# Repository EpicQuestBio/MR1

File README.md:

# MR1 Nanopore Reader (MR1)

[-brightgreen.svg)](#testing--verification)

The **MR1 Nanopore Reader** is an open-source, ultra-low-noise solid-state and biological nanopore sequencer flow cell, low-current transimpedance amplifier, and automated fluidic control system. It integrates high-precision parametric CAD models (`build123d`), ultra-low-leakage analog front-end electronics (KiCad), an automated dual-pump fluidic handler, and an ESP32-S3 high-speed continuous streaming firmware stack.

## Architecture & Overview
The system uses a complete **4-electrode topology** (Working Electrode `WE_POS` / `>PORE_AMP`, Working Sense `WS_CIS` & `WS_CIS_WIDE`, Reference Electrode `RE_TRANS`, Counter Electrode `CE_GNDA`) combined with explicitly driven guards (`GUARD`, `GUARD_WIDE`, `GUARD_CIS_A`, `GUARD_CIS_B`) across a distributed 12-pin interface ($36\text{ mm}$ span) to achieve sub-picoampere sensitivity, neutralize stray capacitance, and distribute mechanical spring forces across the PTFE substrate.

The architecture consists of:
- **Headstage Hardware**: A custom, low-parasitic PTFE/Rogers interposer cartridge that seats a 4x4mm nanopore wafer clamped within silicone PDMS gaskets. It interfaces via gold-plated pogo pins to a low-bias-current transimpedance amplifier (LMP7721) mounted beneath the flowcell.
- **Reader Hardware (MR1)**: An ESP32-S3-driven core processing node operating a continuous 100 kHz SPI DMA data acquisition sequence, dual DACs for precision transmembrane voltage bias, and USB CDC-ACM streaming logic.
- **Pump / Power Subsystem**: A dedicated USB-PD powered board managing automated fluidic dispensing (peristaltic motors), pressure sensing, and SBU-based I2C communication back to the main MR1 host.
- **Data Ingestion Pipeline**: High-throughput IPC software utilizing python scripts (`daq_client.py`) and zeroMQ / WebSocket endpoints to reliably process, structure, decode, and log the real-time electrical data for machine learning basecalling or browser visualization.

## Setup & Prerequisites
To build, modify, or interact with this repository, ensure your environment meets these requirements.

### Toolchain Prerequisites
- **Python**: 3.10+
- **KiCad**: Version 7.0+ (For PCB design modifications and scripting exports)
- **PlatformIO Core (CLI)**: For firmware compilation (`pio run`)
- **OpenSCAD / build123d**: For generating solid body parts.
- **Node.js**: v18+ (For UI and test automation dependencies)

### Environment Setup
Run the bootstrap setup scripts depending on your OS to establish a clean python virtual environment and node module cache.
```bash
# On Linux/macOS
./setup_env.sh

# On Windows (PowerShell)
.\setup_env.ps1
```

Activate the python virtual environment:
```bash
source .venv/bin/activate
```

### Build & Test
You can trigger the comprehensive unit, integration, and dimension-parity tests using the included test suite.
```bash
# Ensure you have activated the virtual environment and built assets
python run_tests.py
# Or directly via pytest
pytest tests/
```

To build and upload firmware to the MR1 reader or the Pump board:
```bash
# Navigate to the target directory
cd MR1_firmware  # or cd Pump_firmware
pio run --target upload
```

## License

This project is dedicated to the public domain under the **CC0 1.0 Universal (CC0 1.0) Public Domain Dedication**.

Created by Lawrence R. Kincheloe III / Molecular Reality Corp (2026).
See the `LICENSE` file for the full text.

---

## Table of Contents

- [Architecture & Overview](#architecture--overview)
- [Setup & Prerequisites](#setup--prerequisites)
- [License](#license)
- [System Architecture](#system-architecture)
- [Project Structure](#project-structure)
- [Quick Start & Environment Setup](#quick-start--environment-setup)
- [Deliverables & Export System](#deliverables--export-system)
- [Hardware Build Pipeline & Board Status](#hardware-build-pipeline--board-status)
- [OpenAuto-CFD & Co-Design](#openauto-cfd--co-design)
- [3D Visualizer & Interactive Inspection](#3d-visualizer--interactive-inspection)
- [KiCad Action Plugin & CLI](#kicad-action-plugin--cli)
- [Testing & Verification](#testing--verification)
- [Hardware & Electronics](#hardware--electronics)
- [ESP32-S3 Firmware](#esp32-s3-firmware)
- [Fluidic Routing & Mold Casting](#fluidic-routing--mold-casting)
- [Documentation Index](#documentation-index)

## System Architecture

```
                       +---------------------------------------+
                       |           Host PC / Laptop            |
                       |  (High-Throughput Binary Telemetry)   |
                       +-------------------+-------------------+
                                           | J1_HOST (USB-C Cable: USB-PD Sink + High-Speed Data)
                                           v
                       +---------------------------------------+
                       |      Pump Module Board (Pump/)        |
                       |  - STUSB4500 Autonomous USB-PD Sink   |
                       |  - TS3USB221 USB 2.0 Streaming Pass   |
                       |  - STM32G431 Control MCU @ 170 MHz    |
                       |  - Dual Honeywell ABP2 Pressure Sens  |
                       |  - Dual DRV8837C Peristaltic Drivers  |
                       |  - Clean Regulated 5V Output Filter   |
                       +-------------------+-------------------+
                                           | J2_MR1 (USB-C Link: +5V_MR1_CLEAN + SBU I2C + USB)
                                           v
                       +---------------------------------------+
                       |         ESP32-S3 MCU (MR1)            |
                       |  Core 1: ADC SPI DMA & USB CDC Stream |
                       |  Core 0: Web Server, Leak & Pump Ctrl |
                       +---------+-------------------+---------+
                                 |                   |
            SPI Bus (100 kHz)    |                   | UART (J22) / SBU I2C
                                 v                   v
     +-----------------------------+        +--------------------------+
     |     AD40xx 16/18-Bit ADC    |        |  Dual Peristaltic Pumps  |
     |   LMP7721 Ultra-Low-Noise   |        |  (Cis & Trans Chambers)  |
     |     Cartridge Amplifier     |        +--------------------------+
     +--------------+--------------+
                    | Gold Pogo Pins (Ultra-low noise shielded)
                    v
     +---------------------------------------------------------+
     |              Hexagonal Cartridge Flow Cell              |
     |  - Cis & Trans Fluidic Chambers ('X' microfluidic)      |
     |  - Cast Silicone Gasket with Nanopore Silicon Wafer     |
     |  - M75x8mm Clamping Torque Cap & Pressure Puck          |
     |  - Conductive Weep Moat / Leak Detection Sensor         |
     +---------------------------------------------------------+
```

---

## Project Structure

```
mr1/
├── src/                          # Parametric CAD models (build123d / Python)
│   ├── cartridge.py              # Flow cell cartridge stack & PCB models
│   ├── housing.py                # Reader and Pump housings, lids, mounting
│   ├── nanopore_wafer_mold.py    # Interlocking two-part resin casting mold
│   ├── torque_cap.py             # M75/M76 ratcheting torque limiter cap
│   ├── adapters.py               # Luer-lock and threaded NPT fluidic adapters
│   ├── connectors.py             # USB-C, JST XH, and bulkhead panel mounts
│   ├── assembly.py               # Full 3D assembly & 3D spline routing sweeps
│   ├── collision_check.py        # Automated 3D BREP collision & clearance checker
│   └── constants.py              # Central engineering & physical parameters
├── MR1/                          # KiCad 10.0 project for Main Reader Board (4-Layer)
├── Amplifier/                    # KiCad 10.0 project for Cartridge Transimpedance Amp (2-Layer)
├── Pump/                         # KiCad 10.0 project for Pump Controller & USB-PD Hub (4-Layer)
├── MR1_firmware/                 # ESP32-S3 C++ firmware (PlatformIO)
│   ├── include/                  # Pinout mapping, binary protocol framing, web portal
│   ├── src/hal/                  # AD40xx SPI DMA ADC, MCP4822 DAC, Leak Detector
│   ├── src/comm/                 # High-speed USB CDC streaming & UART Pump protocol
│   └── src/web/                  # Embedded Web Portal with WebSocket Oscilloscope
├── wiring/                       # WireViz electrical and fluidic harness specs
│   ├── reader_wiring.yaml        # USB-C, motor, and analog pogo wiring harnesses
│   └── reader_tubing.yaml        # FEP, PharMed BPT, and silicone fluidic tubing specs
├── tests/                        # Automated unit, CAD bounds, firmware, and E2E tests
│   ├── test_geometry.py          # Geometric validity and collision regression
│   ├── test_golden_stl_bounds.py # Dimensional assertions against golden models
│   ├── test_connector_bounds.py  # Connector mounting dimensional checks
│   ├── test_firmware_protocol.py # Binary framing, CRC-16, and DAC mapping tests
│   └── test_exports_e2e.py       # Full deliverables validation (141 files)
├── scripts/                      # Build, export, and testing automation
│   ├── export_manager.py         # Universal multi-domain export orchestrator
│   ├── export_all.sh             # POSIX bash export runner
│   └── run_e2e_tests.sh          # POSIX bash end-to-end test runner
├── exports/                      # Generated release deliverables & manifest
├── requirements.txt              # Pinned Python virtual environment dependencies
├── setup_env.sh                  # Virtual environment manager (Linux/macOS/Bash)
├── setup_env.ps1                 # Virtual environment manager (Windows PowerShell)
├── Makefile                      # Standard project build and export targets
├── EXPORTS.md                    # Detailed deliverables and ordering documentation
├── BOM.md                        # Mechanical bill of materials & sourcing links
└── CASTING.md                    # PDMS/Silicone flow cell casting guidelines
```

---

## Quick Start & Environment Setup

### 1. Initialize Python Virtual Environment

The project uses a local virtual environment (`.venv`) for all Python CAD generation, export pipelines, and test suites.

**On Windows (PowerShell):**
```powershell
.\setup_env.ps1
```

**On Linux / macOS / Git Bash:**
```bash
chmod +x setup_env.sh install.sh
./setup_env.sh
```

To verify environment health at any time:
```bash
./setup_env.sh --check        # or powershell -File .\setup_env.ps1 -Check
```

### 2. Required External Tools (Optional for specific export domains)
- **KiCad 10.0 CLI** (`kicad-cli`): Required to generate Gerbers, Drill files, Pick & Place CSVs, BOMs, and PDF schematics.
- **Graphviz** (`dot`): Required by WireViz for rendering graphical wiring and tubing diagrams.
- **PlatformIO Core** (`pio`): Required to compile ESP32-S3 firmware binaries.

---

## Deliverables & Export System

The repository features an automated multi-domain export orchestrator (`scripts/export_manager.py`) managed via GNU Make, shell scripts, or npm:

### Common Commands

```bash
# Export all project deliverables (CAD, KiCad, Wiring, Firmware, and Manifest)
make export

# Or export specific domains
make export-cad        # 3D Solids (STEP/STL) & 2D CNC Profiles (DXF)
make export-kicad      # Gerbers, Drill, POS, BOM, and PDF schematics
make export-wiring     # WireViz wiring harness and fluidic diagrams
make export-firmware   # Compile and stage ESP32-S3 firmware binaries

# Verify manifest and deliverables
make check             # Verify all 141 indexed deliverables exist on disk
make test              # Run unit tests and CAD collision clearance checks
make test-e2e          # Run end-to-end deliverables validation test
```

### Generated Deliverables Inventory (`exports/`)
- **30 STL Meshes**: Ready for 3D printing (SLA resin molds, TPU pusher plates, PETG housings, and PTFE interposer models).
- **22 STEP Models**: Parametric BREP solids for mechanical assembly and CAD exchange.
- **13 DXF Profiles**: 2D profiles for CNC milling polypropylene sheet stock and synchronizing KiCad PCB `Edge.Cuts` (including `Interposer_DXF.dxf` and `Plate_2_Channel_DXF.dxf`).
- **Fab-Ready PCB Archives**: `MR1_Gerbers.zip` (4-layer main board) and `Amplifier_Gerbers.zip` (2-layer amplifier).
- **Manufacturing Documentation**: Pick-and-Place (POS) coordinates, BOM CSVs, and multi-sheet schematic PDFs.
- **Harness Documentation**: WireViz diagrams for internal wiring and 1/8" barb fluidic tubing.
- **ESP32-S3 Firmware**: Staged `firmware.bin`, `bootloader.bin`, and `partitions.bin`.
- **SHA-256 Manifest**: `exports/manifest.json` tracks file sizes and cryptographic hashes for all 159 files for drift detection.

See [EXPORTS.md](EXPORTS.md) for full details and PCB fabrication recommendations.

---

## Hardware Build Pipeline & Board Status

Automated code scanners and reviewers sometimes mistake the repository's PCB source files for static production-ready layouts. The MR1 hardware design pipeline relies on two fundamental principles:

1. **Dynamic Artifact Generation**:
   The `.kicad_pcb` layout files and downstream fabrication deliverables (Gerber layers, NC drill files, BOMs, Pick and Place POS files, multi-sheet PDF schematics) are dynamically generated and reconciled via the repository's automation pipeline (`scripts/export_manager.py`, Python footprint/layout generators, and `kicad-cli`), rather than being maintained as static hand-edited binaries in the working tree.

2. **Current Board Layout & Routing Status**:
   - **`MR1` Main Reader Board** (`MR1/`): 111 footprints placed, placement complete, 0 routed copper tracks.
   - **`Amplifier` Cartridge Board** (`Amplifier/`): 48 footprints placed, placement complete, 0 routed copper tracks.
   - **`Interposer` Microfluidic Board** (`Interposer/`): 33 footprints placed, 9 routed segments.
   - **`Pump` Controller Board** (`Pump/`): 18 footprints placed, procedurally generated stubs — STM32 QFN-48 currently a 1-pad stub with passives and 3D models pending per [`TODO.md`](TODO.md) §22.

For details on Gerber archiving, dynamic export workflows, and hardware version tags, see the [Artifact & Gerber Release Policy in EXPORTS.md](EXPORTS.md#artifact--gerber-release-policy).

---

## OpenAuto-CFD & Co-Design

The **MR1 Nanopore Reader** incorporates the **OpenAuto-CFD** co-design framework ([`openauto.project.json`](openauto.project.json) / [`atlas.project.json`](atlas.project.json)) to bridge Electrical CAD (KiCad), Mechanical CAD (Build123d / OpenSCAD), and Microfluidic Multiphysics into a single automated pipeline.

### Why OpenAuto-CFD?
Nanopore sensing demands precise hydrodynamic and electro-chemical alignment:
1. **Laminar Stokes Flow ($\text{Re} \ll 1$):** With $50\,\mu\text{m} \times 25\,\mu\text{m}$ channels and $10\,\mu\text{L/min}$ delivery, OpenAuto-CFD calculates viscous pressure drops ($\Delta P \approx 6.2\text{ kPa}$) and eliminates turbulent vortex formation.
2. **SiN Membrane Burst Safety:** Free-standing $20\text{ nm}$ silicon nitride membranes rupture at differential pressures $\Delta P_{\text{burst}} \sim 10\text{ mbar}$. OpenAuto-CFD co-simulation balances hydrodynamic resistance across Cis and Trans chambers to prevent wafer fracture.
3. **Dead-Volume & Bubble Prevention:** Eliminates stagnation recirculation zones ($\vec{v} < 0.01 \cdot v_{\text{bulk}}$) that trap air microbubbles or cause analyte sample carryover.
4. **Concentric Kelvin Cell Coupling:** Aligns the 4-electrode Kelvin sensing array on the PTFE interposer directly with the microfluidic chamber aperture.

See the comprehensive [OpenAuto-CFD Guide](docs/OPENAUTO_CFD.md) for full physical derivations and co-simulation specs.

---

## 3D Visualizer & Interactive Inspection

The repository provides a rich multi-layer 3D visualizer powered by `build123d` and `ocp_viewer`:

```bash
# Launch interactive 3D assembly visualizer
npm run visualize
# Or via Python directly:
python src/assembly.py

# Or launch via install script diagnostic flag:
./install.sh --viewer
```

### Visualizer Features
- **Full System Assembly:** Displays the Peristaltic Pump base module, Reader Housing & Tower, 4× Luer Bulkhead Panel Mounts, 7-layer Cartridge Stack (Bottom Pusher Plate, Base Hex Plate, Fitted Gasket, Active PCB, Wafer Gasket, Top Hex Plate, Pressure Puck), and Torque-Lock Cap.
- **3D Swept Tubing Routes:** Renders actual 3D splines for all 5 fluidic paths (`TUBE_PUMP`, `TUBE_FEED`, `TUBE_TRANS_LINE`, `TUBE_WASTE_1`, `TUBE_WASTE_2`) with verified bend radii.
- **X-Ray & Clipping Plane Inspection:** Enables cross-sectional slicing to verify internal gasket compression and pogo pin deflection.
- **WireViz Electrical & Tubing Harnesses:** Generates SVG and HTML diagrams for internal wiring (`wiring/reader_wiring.yaml`) and fluid lines (`wiring/reader_tubing.yaml`) via `npm run export:wiring`.
- **Automated 360° Flythrough Video:** Renders photorealistic rotating orbits using PyVista VTK via `npm run render:flythrough`.

---

## KiCad Action Plugin & CLI

The repository includes a dedicated KiCad Action Plugin and CLI verification engine ([`plugins/openauto_cfd_plugin.py`](plugins/openauto_cfd_plugin.py)) ensuring PCB layouts strictly comply with mechanical, fluidic, and manifest constraints.

### How to Install the Plugin into KiCad
```bash
# Install plugin into active KiCad installation (~/.local/share/kicad/ or %APPDATA%/kicad/)
npm run openauto:install-plugin
# Or via Python:
python plugins/openauto_cfd_plugin.py --install
```

### Using Inside KiCad PCB Editor (GUI)
1. Open any board (`Amplifier.kicad_pcb`, `MR1.kicad_pcb`, `Pump.kicad_pcb`, or `Interposer.kicad_pcb`).
2. Navigate to **Tools $\to$ External Plugins $\to$ OpenAuto-CFD: Co-Design & Clearance Verifier**.
3. The plugin parses the board, checks Edge.Cuts continuity, verifies bounding dimensions against `openauto.project.json`, and displays a comprehensive verification report.

### Standalone CLI & CI/CD Verification
```bash
# Validate all 4 boards in headless mode (Edge.Cuts continuity, dimensions, and net mapping)
npm run openauto:validate

# Synchronize Edge.Cuts dimensions back into the openauto.project.json manifest
npm run openauto:sync
```

---

## Testing & Verification

The project enforces zero physical interference and strict dimensional fidelity across all hardware interfaces:

```bash
# Run the complete test suite (Unit Tests, Collision Checks, Firmware Protocol, Parity, and E2E)
python run_tests.py
```

### Automated Validation Includes:
1. **Golden STL & PCB Bounds**: Asserts dimensions of all generated CAD models against benchmark constraints.
2. **BREP Collision Clearance (6 Independent Suites)**:
   - Cartridge stack component alignment.
   - Housing and lid clearances.
   - M75×8mm external / M76×8mm internal helical thread engagement (0 interference volume).
   - PCB standoff clearances against fluidic lines.
   - Internal component clearance (wiring vs. cartridge solids).
   - Flexible routing collision sweeps against module envelopes.
3. **Spline Bend Radius Validation**: Computes instantaneous curvature along swept routes and verifies compliance with minimum bend radii (Silicone/FEP tubing $\ge 10\text{ mm}$, Wiring $\ge 10\text{ mm}$).
4. **CAD Feature Validation Suite**: Validates 80x60mm rectangular motherboard, hexagonal carrier frame, circular nanopore carrier, mold modes, lid cutouts, and pump case bosses.
5. **Firmware Protocol Tests**: CRC-16 integrity, binary packet serialization (`StreamFrame`), pump packet XOR checksums, and DAC voltage-to-code mapping.
6. **E2E Deliverables Tests**: Validates headers, non-zero file sizes, and SHA-256 hashes of all 159 export deliverables.

---

## Hardware & Electronics

- **MR1 Main Controller Board** (`MR1/`):
  - 4-Layer stackup:
    - Layer 1 (Top Signal): Component placement, USB D+/D-, SPI traces to FPC, DAC outputs
    - Layer 2 (Ground Plane): Split into GNDA (Quiet Analog Ground) and GND (Digital Ground)
    - Layer 3 (Power Plane): Split into Analog Power (VDDA, VSSA) and Digital Power (+3V3, VBUS)
    - Layer 4 (Bottom Signal): Secondary routing, low-speed housekeeping, and auxiliary pours
  - ESP32-S3-MINI-1U MCU with native high-speed USB CDC.
  - Dedicated SPI bus for high-speed ADC sampling.
  - Dual MCP4822 12-bit DACs providing bipolar pore bias voltages (-1.587V to +1.587V) and unblocking pulses.
  - Conductive weep-hole leak detection sensing on GPIO1.
- **PTFE Interposer Circuit Board** (`Interposer/` & `src/cartridge.py`):
  - 55.0 × 51.962 × 0.8 mm hexagonal substrate fabricated on ultra-low-loss PTFE / Rogers RO4350B.
  - Physical and electrical barrier dividing Cis (top) and Trans (bottom) microfluidic chambers.
  - Dual-sided silver chloride (Ag/AgCl) ribbon electrode pads positioned inside the Cis ($30^\circ$) and Trans ($210^\circ$) flow channels.
  - Central 6.20 × 6.20 mm diamond cutout ($45^\circ$) allowing the silicone gasket protrusion to seal directly around the silicon nanopore wafer.
  - 12-pin guarded ENIG landing array (`PogoPin_Target_12Pin_Distributed`) flanking high-impedance sense lines (`WS_CIS`, `RE_TRANS`) with driven low-impedance `GUARD` pins.
  - Hermetically clamped between `Cast_Nanopore_Wafer_Gasket` (top) and `Fitted_Amplifier_Gasket` (bottom).
- **Cartridge Transimpedance Amplifier** (`Amplifier/`):
  - 2-Layer 0.8 mm ultra-thin board designed for direct insertion into the flow cell stack.
  - LMP7721 ultra-low input bias current amplifier (sub-femtoampere leakage).
  - Low-leakage guard rings and driven shields guarding the high-impedance nanopore input node.
  - Direct connection to flow cell via gold-plated Mill-Max pogo pins.
- **Pump Controller & USB-PD Hub Board** (`Pump/` & `src/cartridge.py`):
  - 4-Layer 1.6 mm board (88.0 × 88.0 mm) fitting within the `Housing_Pump_Case` internal pocket.
  - **Dual USB-C Receptacles**:
    - `J1_HOST` at $X = -15.0\text{ mm}$ (top edge): USB-PD Sink + Host laptop data interface.
    - `J2_MR1` at $X = +15.0\text{ mm}$ (top edge): Regulated clean 5V power output to MR1 Reader + SBU I2C control link.
    - Perfectly aligned to the $12 \times 6\text{ mm}$ cutouts on `Housing_Pump_Case` rear wall ($Y = 55.0\text{ mm}$).
  - **High-Speed USB 2.0 Pass-Through**: TI TS3USB221 multiplexer (>1.1 GHz bandwidth, insertion loss < 0.5 dB) passes 100 kHz continuous ADC telemetry straight through to the laptop without MCU latency.
  - **STUSB4500 Autonomous USB-PD Sink**: Automatically negotiates 9V/12V/15V/20V profiles from USB-PD power sources.
  - **Clean +5V Output Subsystem**: Synchronous step-down buck converter (36V/3A) + TPS22916 soft-start load switch + LC $\pi$-filter ensuring ultra-low ripple 5V power for MR1's analog frontend.
  - **STM32G431CBU6 Control MCU**: ARM Cortex-M4 @ 170 MHz orchestrating precision TIM1 PWM peristaltic velocity control, I2C telemetry, and hardware emergency stop gating.
  - **Dual Honeywell TruStability / ABP2 Pressure Transducers**:
    - Transducer 1 (0-15 psi gauge): Real-time pressure monitoring on Cis chamber feed line.
    - Transducer 2 (0-5 psi gauge): Real-time pressure monitoring on Trans chamber recirculation line.
  - **Dual TI DRV8837C Motor Drivers**: 1.8A peak H-bridge drivers with hardware shutdown interlock directly connected to the weep moat leak detector.

---

## ESP32-S3 Firmware

Located in `MR1_firmware/` (ESP32-S3 Main Reader) and `Pump_firmware/` (STM32G431 Peristaltic Pump & USB-PD Hub):
- **Dual-Core Architecture**:
  - **Core 1**: Dedicated to continuous 100 kHz SPI DMA ADC sampling and high-throughput USB CDC streaming.
  - **Core 0**: Handles Wi-Fi AP/station management, AsyncWebServer, WebSocket oscilloscope telemetry, and pump control.
- **High-Throughput Binary Protocol**: Frames of 64 decimated/raw samples packed with sequence IDs, 64-bit microsecond timestamps, and CRC-16 checksums.
- **USB-C SBU Auto-Polarity Detection**: Dynamic GPIO-matrix sensing on SBU1/SBU2 pins automatically determines clock (SCL) and data (SDA) orientation for I2C communication to external pump modules, working seamlessly regardless of cable flip.
- **Embedded Web Oscilloscope**: Live HTML5 Canvas visualization accessible via browser over Wi-Fi without needing host drivers.

### Host 100 kHz Streaming DAQ Client (`scripts/daq_client.py`)

A high-performance Python client for acquiring continuous 100 kHz binary telemetry from the MR1 Reader:

```bash
# Live acquisition with terminal dashboard and CSV logging
python scripts/daq_client.py --port COM3 --bias 180.0 --output data.csv

# Run mock simulation mode (generates baseline ionic current & DNA translocation events)
python scripts/daq_client.py --mock --duration 5.0 --output simulation.csv

# Execute SBU I2C polarity auto-detection and start pump
python scripts/daq_client.py --port COM3 --sbu-detect --pump 60
```

- **Binary Frame Synchronization**: Synchronizes on `"SENT"` magic word (`0x53454E54` / little-endian `b"TNES"`).
- **CRC-16-CCITT Verification**: 100% integrity validation on every 146-byte packet.
- **Pore Current Conversion**: Converts differential 16-bit counts to Amperes ($I_{\text{pore}} = V_{\text{adc}} / R_f$, default $R_f = 1\text{ G}\Omega \implies 1\text{ V}/1\text{ nA}$).
- **Real-Time Telemetry Dashboard**: Live sample rate (kS/s), data throughput (KB/s), dropped frame count, RMS current noise, pump status, and leak monitoring.

---

## Fluidic Routing & Mold Casting

- **Standardized Tubing**: All microfluidic connections standardize on **1/8" ID $\times$ 1/4" OD** tubing and 1/8" hose barb panel-mount fittings.
- **Fluid Lines**:
  - `TUBE_PUMP`: PharMed BPT (0.12 m) — Buffer reservoir $\to$ Peristaltic pump.
  - `TUBE_FEED`: FEP (0.22 m) — Pump $\to$ Cis chamber inlet ($210^\circ$).
  - `TUBE_TRANS_LINE`: PEEK (0.18 m) — Trans chamber outlet ($150^\circ$) $\to$ Waste.
  - `TUBE_WASTE_LINES` ($\times 2$): Silicone (0.25 m) — Cis outlet ($30^\circ$) and Trans inlet ($330^\circ$).
- **Gasket Fabrication**: Two-part resin casting mold (`Nanopore_Wafer_Mold_Left` and `Right`) designed for casting degassed PDMS (Sylgard 184) or high-compliance silicone around the silicon nanopore wafer. See [CASTING.md](CASTING.md) for detailed surface preparation, degassing, and curing procedures.

---

## Documentation Index

### Open Source Governance & Policies
- [CONTRIBUTING.md](CONTRIBUTING.md): Engineering guidelines, code style, and pull request workflow.
- [CODE_OF_CONDUCT.md](CODE_OF_CONDUCT.md): Contributor Covenant v2.1 standards and pledge.
- [SECURITY.md](SECURITY.md): Security vulnerability reporting policy and electrical safety bounds.
- [CITATION.cff](CITATION.cff): Academic citation metadata for research and publications.
- [LICENSE](LICENSE): CC0 1.0 Universal (CC0-1.0) Public Domain Dedication.

### Hardware & Manufacturing Specifications
- [BOM.md](BOM.md): Complete mechanical, fluidic, PCB, and active electronic bill of materials with sourcing links.
- [EXPORTS.md](EXPORTS.md): Complete export deliverables catalog, fab ordering specifications, and drift tracking.
- [CASTING.md](CASTING.md): Engineering guide for casting ultra-low-noise PDMS gaskets.
- [PROJECT.md](PROJECT.md): Project architecture, interface contracts, and milestone tracking.
- [TODO.md](TODO.md): Development roadmap and completed porting phases.

### Firmware & Protocols
- [MR1 Reader Firmware](MR1_firmware/README.md): ESP32-S3 dual-core firmware architecture, SPI DMA ADC, and web oscilloscope.
- [Pump Hub Firmware](Pump_firmware/README.md): STM32G431 peristaltic motor control, STUSB4500 USB-PD, and pressure monitoring.
- [DAQ Streaming Protocol](docs/DAQ_STREAMING_SPEC.md): Binary stream framing, CRC-16 checksums, and 100 kHz sample encoding.
- [MR1 Data Exchange Spec](docs/MR1_DATA_EXCHANGE_SPEC.md): Inter-board SBU I2C and UART communications.
- [Interposer 4-Electrode Spec](docs/INTERPOSER_FOUR_ELECTRODE_SPEC.md): Gamry 4-electrode topology and driven guard architectures.
- [Weep Moat Interlock Spec](docs/ECO_WEEP_SENSE_BUFFER_INTERLOCK.md): Leak detection sensor and hardware power cutoff circuitry.

### Co-Design, Simulation & Tools
- [Micropore & Salt Aperture Configurations](docs/MICROPORE_NACL_CONFIGURATIONS.md): Working configuration matrix and simulation analysis for 10 µm and 100 µm pores in NaCl.
- [Dual-Route TIA Netlist & BOM](docs/DUAL_ROUTE_AMPLIFIER_NETLIST_BOM.md): Complete point-to-point netlist, component tolerances, and recommended manufacturer BOM for Route 1 (LMP7721) and Route 2 (OPA192).
- [OpenAuto-CFD & 3D Visualizer Guide](docs/OPENAUTO_CFD.md): Multiphysics co-simulation, interactive 3D assembly visualizer (`ocp_viewer`), and KiCad action plugin documentation.
- [OpenAuto Project Manifest](openauto.project.json): Single-source-of-truth hardware manifest linking ECAD, MCAD, fluidics, and harnesses.

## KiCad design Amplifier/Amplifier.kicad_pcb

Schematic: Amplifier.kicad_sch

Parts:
C1: 2pF; C_0402_1005Metric; LCSC C161316
C3: 15pF; C_0402_1005Metric; LCSC C33148
C6, C9, C14, C20: 100nF; C_0402_1005Metric; LCSC C49678
C7, C8: 10nF; C_0402_1005Metric; LCSC C1525
C10, C12, C19, C31, C32, C33, C34, C39: 100nF; C_0402_1005Metric; LCSC C15255
C11: 4.7u; C_0402_1005Metric; Manufacturer_Part_Number JMK107C6475KA-T; LCSC C19702
C29, C30: 10pF; C_0402_1005Metric; LCSC C1548
C35: 10u; C_0402_1005Metric; MPN GRM21BR61H106KE43K; LCSC C1713
C40, C42: 100nF; C_0402_1005Metric; Mouser PN 710-885012205037; LCSC C15255
C41: 1nF; C_0402_1005Metric; LCSC C1523
D82: MBR0540; D_SOD-123; MPN MBR0540L-TP; LCSC C5204747
FB1, FB2: HZ0402A152R-10; L_0402_1005Metric; LCSC C442654
J7: Conn_01x14_MountingPin; Amphenol_F32R-1A7x1-11014_1x14-1MP_P0.5mm_Horizontal; LCSC C2856818
NT3, NT4, NT5, NT6, NT7, NT8: NetTie_2; NetTie-2_SMD_Pad0.5mm
P1, P3, P4, P6, P7, P8, P9, P10, P11, P12: PogoPin_MillMax_SMT_1Pin
P2, P5: PogoPin_MillMax_SMT_1Pin_Guarded; PogoPin_SMT_Circle_Guard_Notched
Q3: 2N7002; SOT-23; LCSC C8545
R1: 1G; R_0402_1005Metric; LCSC HVC0805T1007JET
R3, R5: 1K; R_0402_1005Metric; LCSC C17513
R4: 100; R_0402_1005Metric; LCSC C25097
R6, R9: 1K; R_0402_1005Metric; LCSC C25149
R8: 100; R_0402_1005Metric; LCSC C17408
R10, R14, R15: 100k; R_0402_1005Metric; LCSC C60491
R16: 1M; R_0402_1005Metric; LCSC C25488
R27, R41: 27; R_0402_1005Metric; MPN RC0402JR-0727RL; LCSC C25078
R28, R29, R30, R31, R32, R33: 49.9; R_0402_1005Metric; MPN RC0402JR-0727RL; LCSC C4074199
R43, R44, R45, R46: 499 (0.1%); R_0402_1005Metric; LCSC C25132
SYM1: SYM_Arrow45_Large; Fluid_Overlay_SILKSCREEN_ONLY
U2: LMP7721; SOIC-8_3.9x4.9mm_P1.27mm; Mouser PN 926-LMP7721MA/NOPB
U5: OPA2192IDR; SOIC-8_3.9x4.9mm_P1.27mm; MPN OPA2192IDR; LCSC C110074
U6: ADA4940-1xCP; LFCSP-16-1EP_3x3mm_P0.5mm_EP1.3x1.3mm_ThermalVias; MPN ADA4940-1ACPZ-RL; LCSC C529241
U13: AD40xxBRMZ; MSOP-10_3x3mm_P0.5mm; MPN AD4011BCPZ-RL7; LCSC C539308
U14: LP5907MFX-1.8; SOT-23-5; MPN LP5907MFX-1.8/NOPB; LCSC C92498
U16: LTC6268xS8; SO-8_3.9x4.9mm_P1.27mm; MPN LTC6268IS8#TRPBF; LCSC C689169
U17: ADG1219BRMZ; MSOP-8_3x3mm_P0.65mm; MPN ADG1219BRMZ; LCSC C206796

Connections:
+1V8: C11.1, U13.2 (VDD), U14.5 (OUT)
+3.3VA: C33.1, FB1.2, FB2.1, R14.1, U13.10 (VIO)
+3V3: FB1.1, J7.1, U17.1 (EN)
/>PORE_AMP: J7.14, P9.1 (PIN_1)
/CE_GNDA: NT8.1, P7.1 (PIN_1)
/GDAC_CLK: R31.1, U13.8 (SCK)
/GDAC_EN: R29.1, U13.6 (CNV)
/GDAC_SDI: R30.1, U13.9 (SDI)
/GDAC_SDO: R28.1, U13.7 (SDO)
/GNDA_SHLD: P1.1 (PIN_1)
/GUARD: NT3.1, NT5.2, P4.1 (PIN_1), P5.2 (GUARD), P6.1 (PIN_1), U2.2 (NC), U2.7 (NC)
/GUARD_WIDE: NT5.1, P2.2 (GUARD), P3.1 (PIN_1), U5.6 (-), U5.7
/RE_TRANS: P8.1 (PIN_1), R6.2, R9.2
/ROUTE_SEL: R33.1, U17.8 (IN)
/R_WEEP_GATE: D82.1 (K), R15.2, R16.1
/R_WEEP_LIM: P11.1 (PIN_1), R15.1
/R_WEEP_PULL: Q3.3 (D), R14.2, U14.3 (EN)
/Route1_OUT: C9.1, R3.1, U16.6, U17.7 (SA)
/Route2_OUT: R32.2, U17.5 (SB)
/SHIELD: NT7.2
/SHIELD_AMP: J7.MP (MountPin), NT4.2
/Signal_Return: R45.1, U17.6 (D)
/Vbias: C6.1, C14.1, C35.1, NT3.2, R4.1, R6.1, R9.1, U2.1 (+), U5.3 (+), U5.5 (+), U13.1 (REF), U16.1 (NC), U16.4 (NC)
/Virtual_Ground: C9.2, R3.2, R4.2, U16.2 (-)
/WS_CIS: C1.2, P5.1 (SIG), R1.2, U2.8 (-)
/WS_CIS_WIDE: C3.2, P2.1 (SIG), R10.2, U5.2 (-)
GND: J7.2, J7.8
unnamed: C1.1, R1.1, R8.2, U2.4
unnamed: C39.1, NT7.1
unnamed: J7.3, R31.2
unnamed: J7.4, R33.2
unnamed: J7.5, R28.2
unnamed: J7.6, R29.2
unnamed: J7.7, R30.2
unnamed: Q3.1 (G), R16.2
unnamed: C3.1, R10.1, R32.1, U5.1
unnamed: R44.2, U6.4 (+FB)
unnamed: R45.2, R46.2, U6.2 (+IN)
unnamed: R27.1, U6.10 (+OUT)
unnamed: R46.1, U6.1 (-FB)
unnamed: R43.2, R44.1, U6.3 (-IN)
unnamed: R41.1, U6.11 (-OUT)
unnamed: C29.2, C41.1, R27.2, U13.3 (IN+)
unnamed: C30.1, C41.2, R41.2, U13.4 (IN-)
unnamed: C34.1, FB2.2, U14.1 (IN)
unnamed: R5.1, R8.1, U16.3 (+)
VDDA: C7.1, C10.1, C19.1, C31.1, C40.1, J7.10, U2.6 (V+), U5.8 (V+), U6.5 (+Vs), U6.6 (+Vs), U6.7 (+Vs), U6.8 (+Vs), U16.7 (V+), U17.2 (VDD)
VSSA: C8.1, C12.1, C20.1, C32.1, C42.1, J7.12, U2.3 (V-), U5.4 (V-), U6.13 (-Vs), U6.14 (-Vs), U6.15 (-Vs), U6.16 (-Vs), U16.5 (V-), U17.4 (VSS)

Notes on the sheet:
SM10B-SRSS-TB
3. Selecting the Precision ADC To capture <1µV signals, you need a 24-bit or 32-bit Delta-Sigma ADC. The standard 12-bit or 16-bit SAR ADCs used in microcontrollers will not see the signal floor you have created. Top Recommendations: TI ADS1261 (24-bit / 32-bit mode): Why: It has a built-in PGA (Pr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
Ceramic capacitors are piezoelectric – mechanical vibrations and noises will create charge across the capacitor. Be careful when using ceramic caps in the input, integration, feedback or biasing networks.
LTC6268
consider cat 7 flat ribbon cable, 8 pairs, shielded
low noise voltage converters
Stage 2 Voltage Amplifier
R1 1206
Stage 1: Transimpedance Amp
Stability in ultra-low noise regulators is dictated by the **Output Capacitance ()** and the **Noise Reduction Capacitance ()**. If these ratios are wrong, the LDO will oscillate, turning your "clean" power supply into a radio transmitter. ### 1. The LDO Component Values (The Critical Stage) These 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
https://www.vpi.us/bulk-cable-sf/super-flat-cat7-736#idTab9
R_DAMP
MG Chemicals 422C conformal coating
amplifier board
RF-damping capacitor
For high-speed nanopore sensing, the answer is definitive: **Do NOT tie them together.** You should use **Separate Voltage References** (or at least strictly buffered separate paths) for your ADC and your Bias Driver. Here is the engineering reality of why sharing a "Reference Rail" will introduce 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
No, the schematic recipe I provided above is **Fixed Gain (10x)**. It uses a standard resistor, so the zoom level is locked. Since you are removing the MAX9939 (which *was* a variable gain amplifier), you likely want to keep that functionality—especially since Nanopores vary wildly in current. A 1 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
PTFE (ZYF255DA): Dk .approx 2.55
499Ω Metal Film Resistor
we need to play back a waveform
250ft 32AWG CAT7 STP Solid, 0.075" Super Flat Bulk Ethernet Bare Copper Cable - White.
Using an **Optically Isolated Current Source (LED + Photodiode)** is the "Ferrari" of dummy loads for nanopore amplifiers. While the resistor method (like in the EarlGrey PDF) is great for checking baseline noise, the LED/Photodiode method is superior for checking **bandwidth** and **step response*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
pins for holding the board in place while applying adhesive https://www.mcmaster.com/98378A208/
SSH-003T-P0.2-H #32 to #28 (0.032 to 0.081) 0.4 to 0.8 23,000
SHR-10V-S
C2 and C3 X5R

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
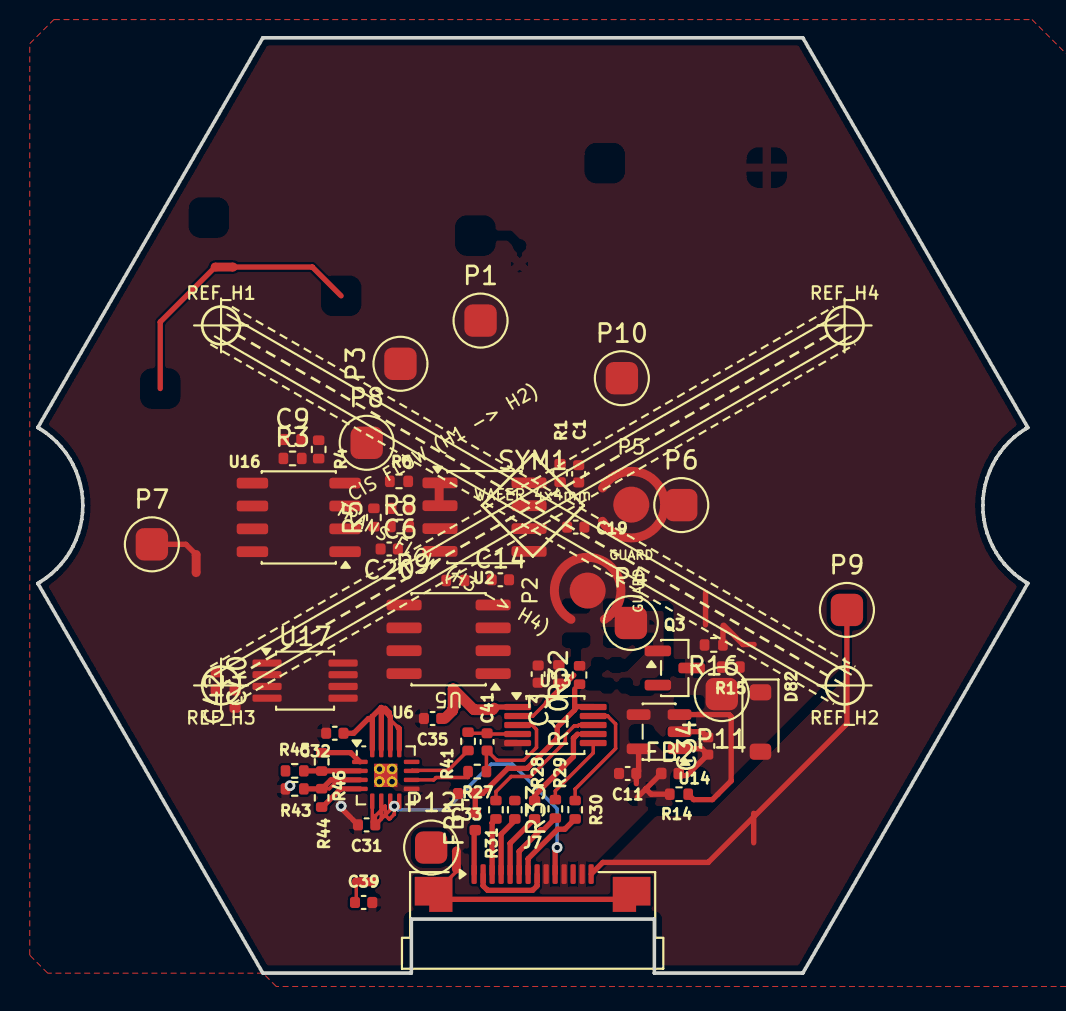
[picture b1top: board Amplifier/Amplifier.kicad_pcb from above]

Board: 2 copper layers, 55.0 x 52.0 mm, 70 parts (0 on the bottom side), 47 nets.

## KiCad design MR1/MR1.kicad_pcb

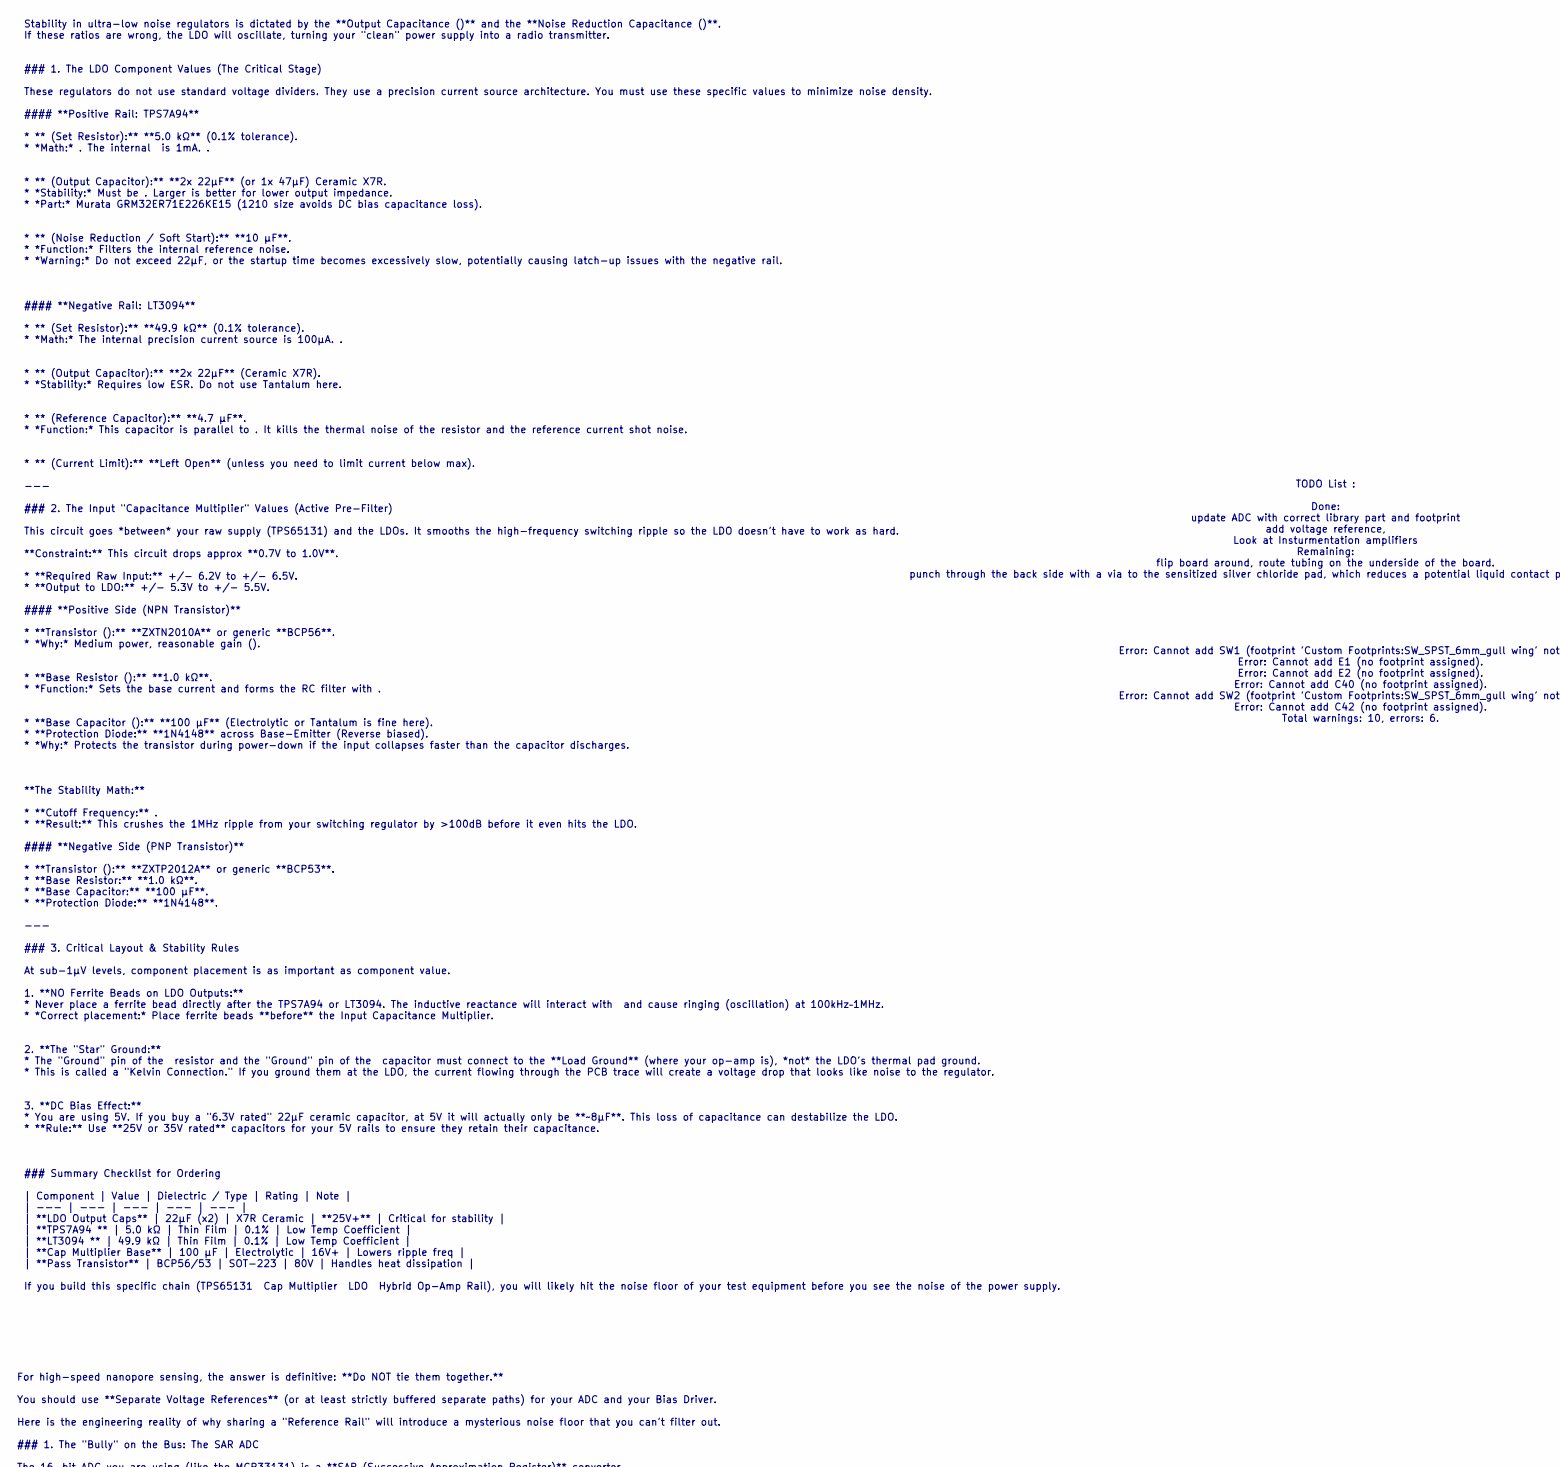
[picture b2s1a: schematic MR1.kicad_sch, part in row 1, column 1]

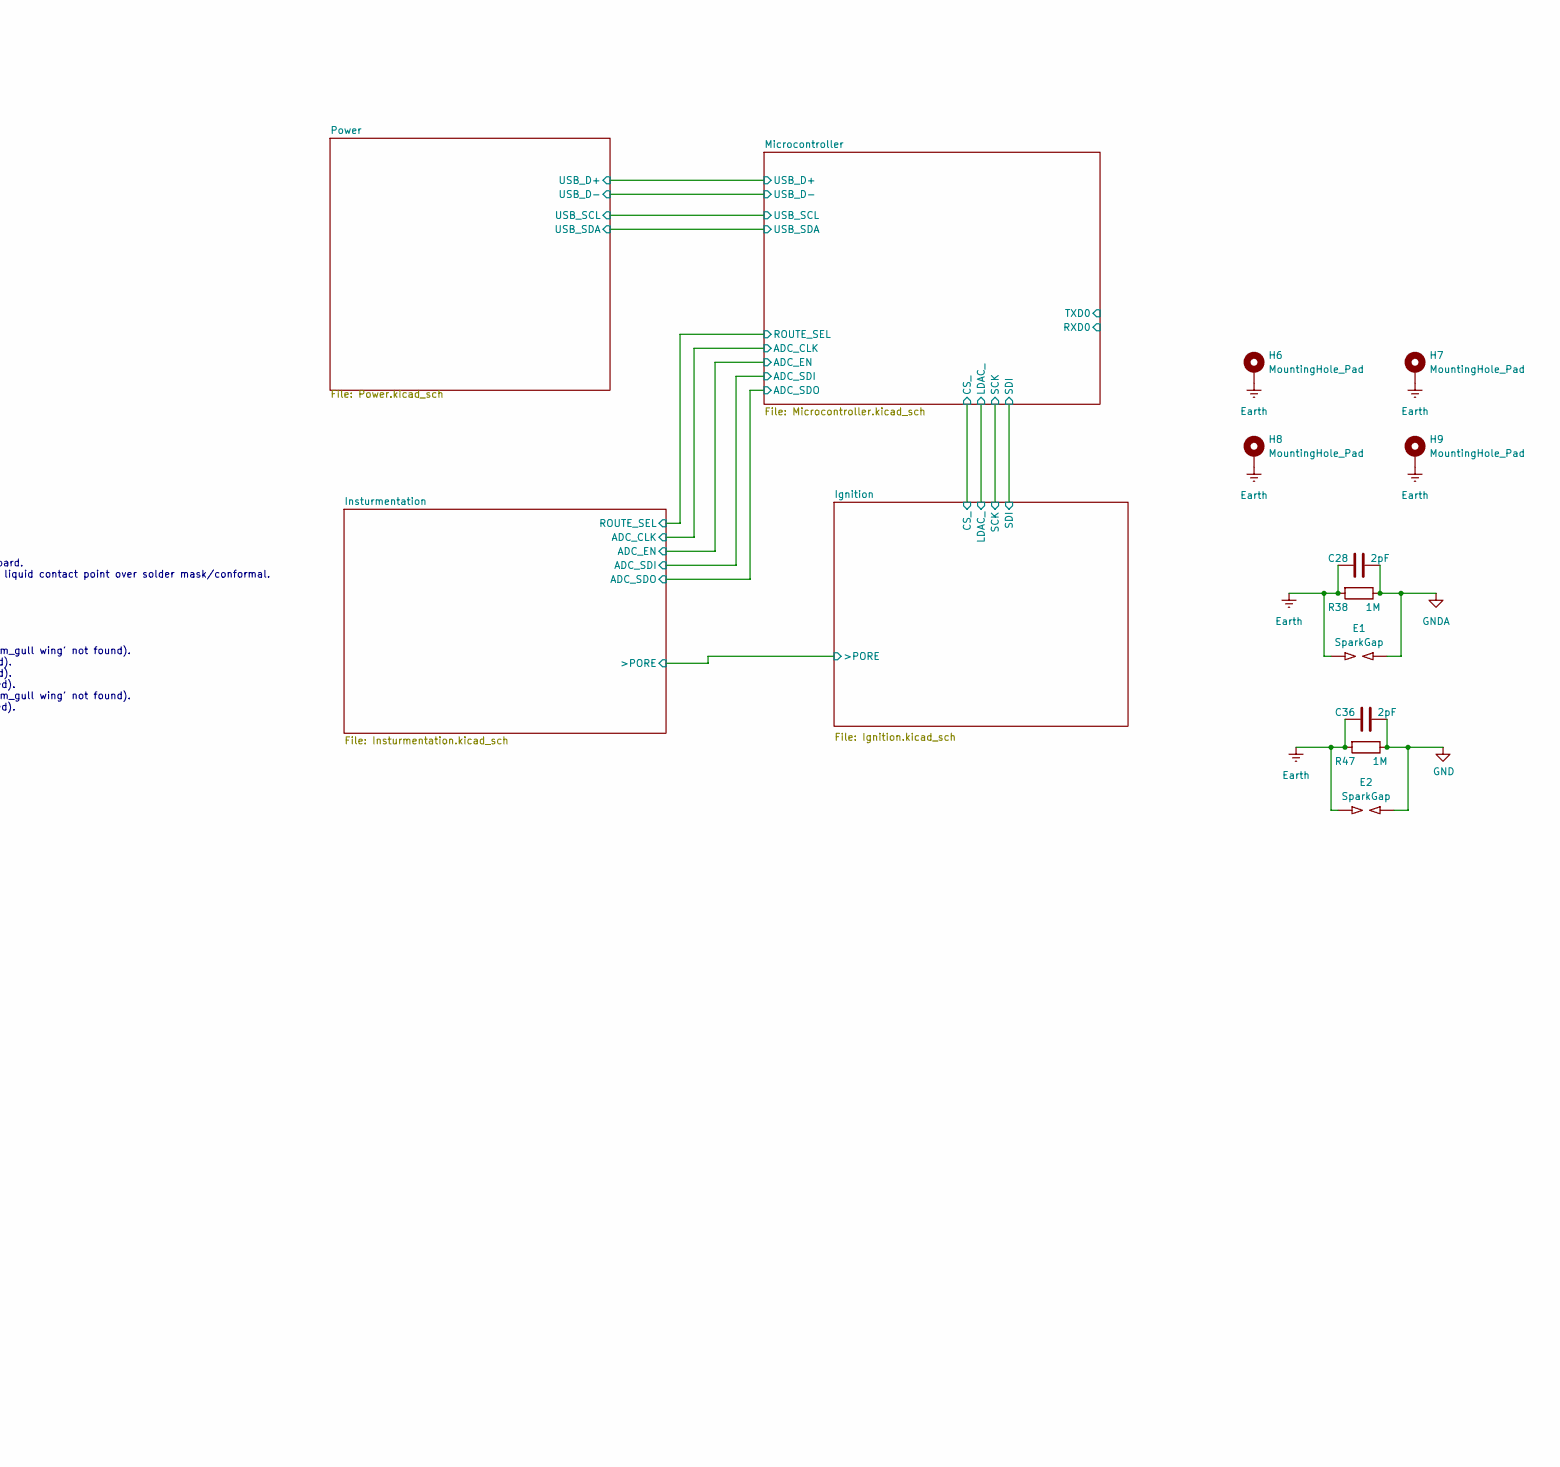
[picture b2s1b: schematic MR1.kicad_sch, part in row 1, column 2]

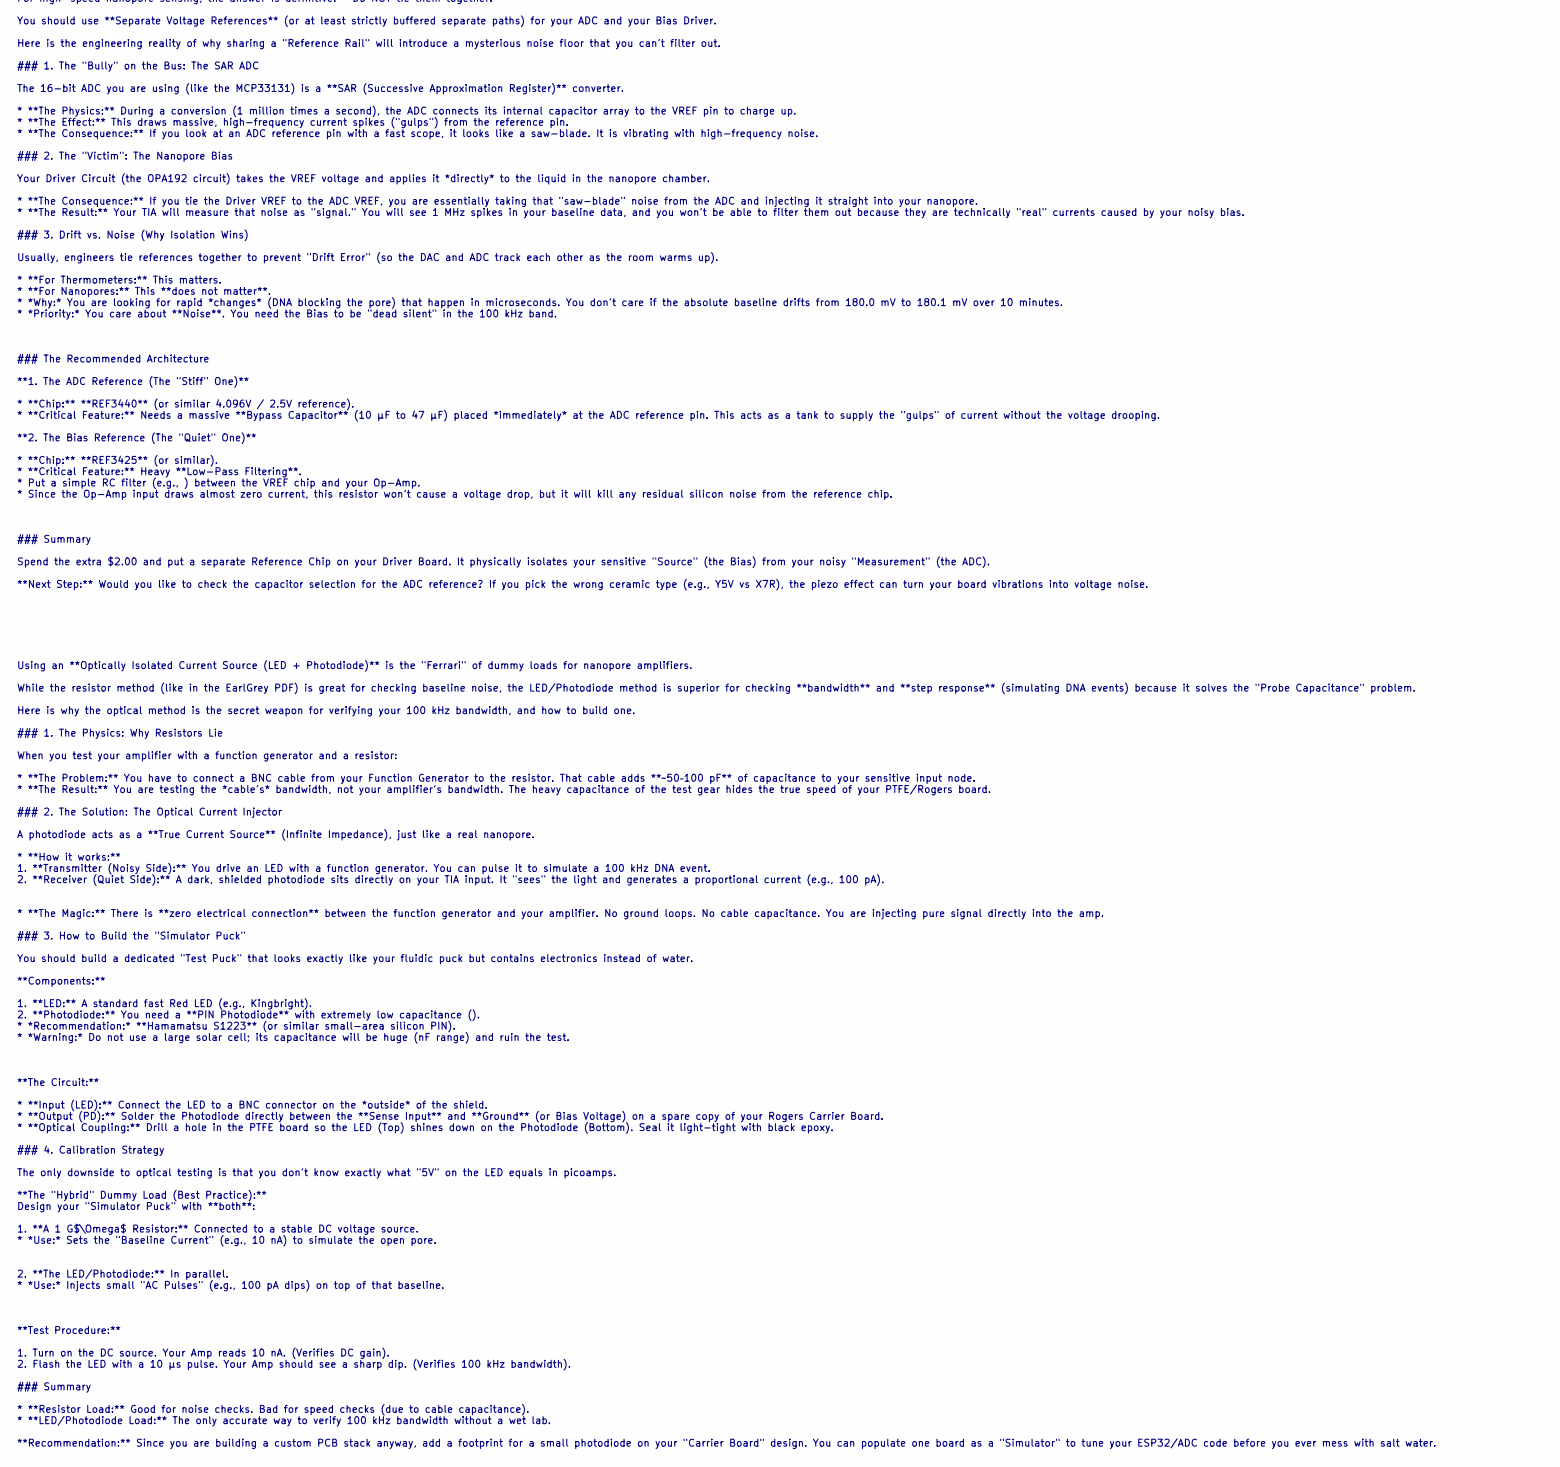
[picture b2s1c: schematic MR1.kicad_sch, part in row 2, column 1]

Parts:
C28, C36: 2pF; C_0402_1005Metric; LCSC C161316
E1, E2: SparkGap; SolderJumper-2_P1.3mm_Open_TrianglePad1.0x1.5mm
H6, H7, H8, H9: MountingHole_Pad; MountingHole_3.2mm_M3_Pad_Via
R38, R47: 1M; R_0402_1005Metric; LCSC C25488

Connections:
Earth: C28.2, C36.2, E1.1, E2.1, H6.1 (1_1), H7.1 (1_1), H8.1 (1_1), H9.1 (1_1), R38.2, R47.2; also elsewhere on the board
GND: C36.1, E2.2, R47.1; also elsewhere on the board
GNDA: C28.1, E1.2, R38.1; also elsewhere on the board

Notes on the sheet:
Stability in ultra-low noise regulators is dictated by the **Output Capacitance ()** and the **Noise Reduction Capacitance ()**. If these ratios are wrong, the LDO will oscillate, turning your "clean" power supply into a radio transmitter. ### 1. The LDO Component Values (The Critical Stage) These 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
For high-speed nanopore sensing, the answer is definitive: **Do NOT tie them together.** You should use **Separate Voltage References** (or at least strictly buffered separate paths) for your ADC and your Bias Driver. Here is the engineering reality of why sharing a "Reference Rail" will introduce 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
TODO List : Done: update ADC with correct library part and footprint add voltage reference, Look at Insturmentation amplifiers Remaining: flip board around, route tubing on the underside of the board. punch through the back side with a via to the sensitized silver chloride pad, which reduces a pote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
Using an **Optically Isolated Current Source (LED + Photodiode)** is the "Ferrari" of dummy loads for nanopore amplifiers. While the resistor method (like in the EarlGrey PDF) is great for checking baseline noise, the LED/Photodiode method is superior for checking **bandwidth** and **step response*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
Error: Cannot add SW1 (footprint 'Custom Footprints:SW_SPST_6mm_gull wing' not found). Error: Cannot add E1 (no footprint assigned). Error: Cannot add E2 (no footprint assigned). Error: Cannot add C40 (no footprint assigned). Error: Cannot add SW2 (footprint 'Custom Footprints:SW_SPST_6mm_gull wing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
